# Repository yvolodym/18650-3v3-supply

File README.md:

# 18650-3v3-supply

Stabile 3,3-V-Versorgung aus einer 18650-Li-Ion-Zelle, inklusive USB-Ladung und Zellschutz.
KiCad-Projekt (KiCad 10).

## Blockschaltbild

```mermaid
flowchart LR
    USB["USB-C 5 V<br/>(P1)"] -->|VBUS| CHG["TP4056 (U1)<br/>Laden 0,9 A"]
    CHG -->|BAT+| BAT["18650 (BT1)<br/>+ DW01A / FS8205A<br/>Schutz"]
    BAT -->|BAT+| BOOST["MT3608 (U3)<br/>Boost 4,0 V<br/>über SS14"]
    BOOST -->|VBOOST| LDO["AP2112K-3.3 (U4)<br/>LDO"]
    LDO -->|+3V3| OUT["3,3 V<br/>(J1)"]
    BAT -->|"R8/R9 ÷2"| SENSE["VBAT_SENSE<br/>(J1 Pin 3)"]
```

1. **Laden** – USB-C-Buchse (P1, 5 V) → TP4056 (U1), Ladestrom ca. 0,9 A (R1 = 1,2 kΩ an PROG,
   laut Datenblatt-Tabelle; für 1 A: R1 = 1,1 kΩ). CC1/CC2 je 5,1 kΩ (R10/R11) nach GND, damit
   USB-C-Netzteile 5 V liefern.
   LEDs: D1 rot = lädt, D2 grün = voll. TEMP liegt an GND (NTC-Überwachung deaktiviert).
2. **Akku + Schutz** – 18650-Zelle (BT1) zwischen BAT+ und BAT−, DW01A (U5) + Dual-MOSFET FS8205A (Q1).
   Abschaltung bei Überladung 4,3 V / Tiefentladung 2,4 V / Überstrom.
   Systemmasse GND = P− (hinter dem FS8205A).
3. **Boost** – MT3608 (U3) mit L1 = 22 µH (≥ 2 A) und Schottky D3 (SS14) auf ca. 4,0 V (Netz `VBOOST`):
   `Vout = 0,6 V × (1 + R6/R7) = 0,6 × (1 + 22k/3,9k) ≈ 3,98 V`.
   Für 5 V Ausgang: R7 = 3 kΩ. Bei vollem Akku (4,2 V) taktet der Boost nur noch wenig (4,2 V − U_F(SS14) < 3,98 V), der LDO regelt.
4. **LDO** – AP2112K-3.3 (U4) aus `VBOOST` → stabile 3,3 V an J1 (Eingangsbereich Akku 2,4 … 4,2 V, untere Grenze = DW01A-Abschaltung).

**VBAT_SENSE:** Akkuspannung / 2 über Teiler R8/R9 (2 × 100 kΩ) für einen ADC.
Bei ca. 1,5 V (= 3,0 V Akku) sollte der Verbraucher in den Schlafmodus gehen.

## Anschlüsse

| Ref | Funktion | Pins |
|-----|----------|------|
| P1  | USB_5V_IN | USB-C-Buchse (GCT USB4105), nur VBUS/GND/CC1/CC2 genutzt |
| J1  | OUT_3V3   | 3-polig JST-EH (1 = +3V3, 2 = GND, 3 = VBAT_SENSE) |

## Stückliste (Hauptbauteile)

| Ref | Wert |
|-----|------|
| U1 | TP4056 Lade-IC |
| U5 | DW01A Akkuschutz |
| Q1 | FS8205A Dual-N-MOSFET |
| U3 | MT3608 Boost-Wandler |
| U4 | AP2112K-3.3 LDO |
| BT1 | 18650 Li-Ion |
| L1 | 22 µH / ≥ 2 A |
| D1, D2 | LED rot / grün |
| D3 | SS14 Schottky |
| C1–C8 | 10 µF, 10 µF, 100 nF, 3 × 22 µF, 1 µF, 10 µF |
| R1–R11 | 1,2k, 1k, 1k, 100R, 1k, 22k, 3,9k, 100k, 100k, 5,1k, 5,1k |
| P1 | USB-C-Buchse GCT USB4105 |
| J1 | JST EH 3-polig |

## Dateien

| Datei | Inhalt |
|-------|--------|
| `Akku_3V3_Versorgung.kicad_pro` | KiCad-Projekt |
| `Akku_3V3_Versorgung.kicad_sch` | Schaltplan |
| `Akku_3V3_Versorgung.kicad_pcb` | Platine (noch leer / nicht geroutet) |
| `Akku3V3.kicad_sym` | Projektlokale Symbolbibliothek |
| `sym-lib-table` | Bindet `Akku3V3` über `${KIPRJMOD}` ein |

## Status

- [x] Schaltplan
- [ ] Footprints zuweisen
- [ ] PCB-Layout
- [ ] Fertigungsdaten (Gerber/Bohrdaten werden nicht eingecheckt, siehe `.gitignore`)

## Lizenz

Copyright © 2026 Eugen Vladimirski

Dieses Projekt steht unter der **CERN Open Hardware Licence Version 2 – Strongly Reciprocal**
(SPDX: `CERN-OHL-S-2.0`), siehe [`LICENSE`](LICENSE).

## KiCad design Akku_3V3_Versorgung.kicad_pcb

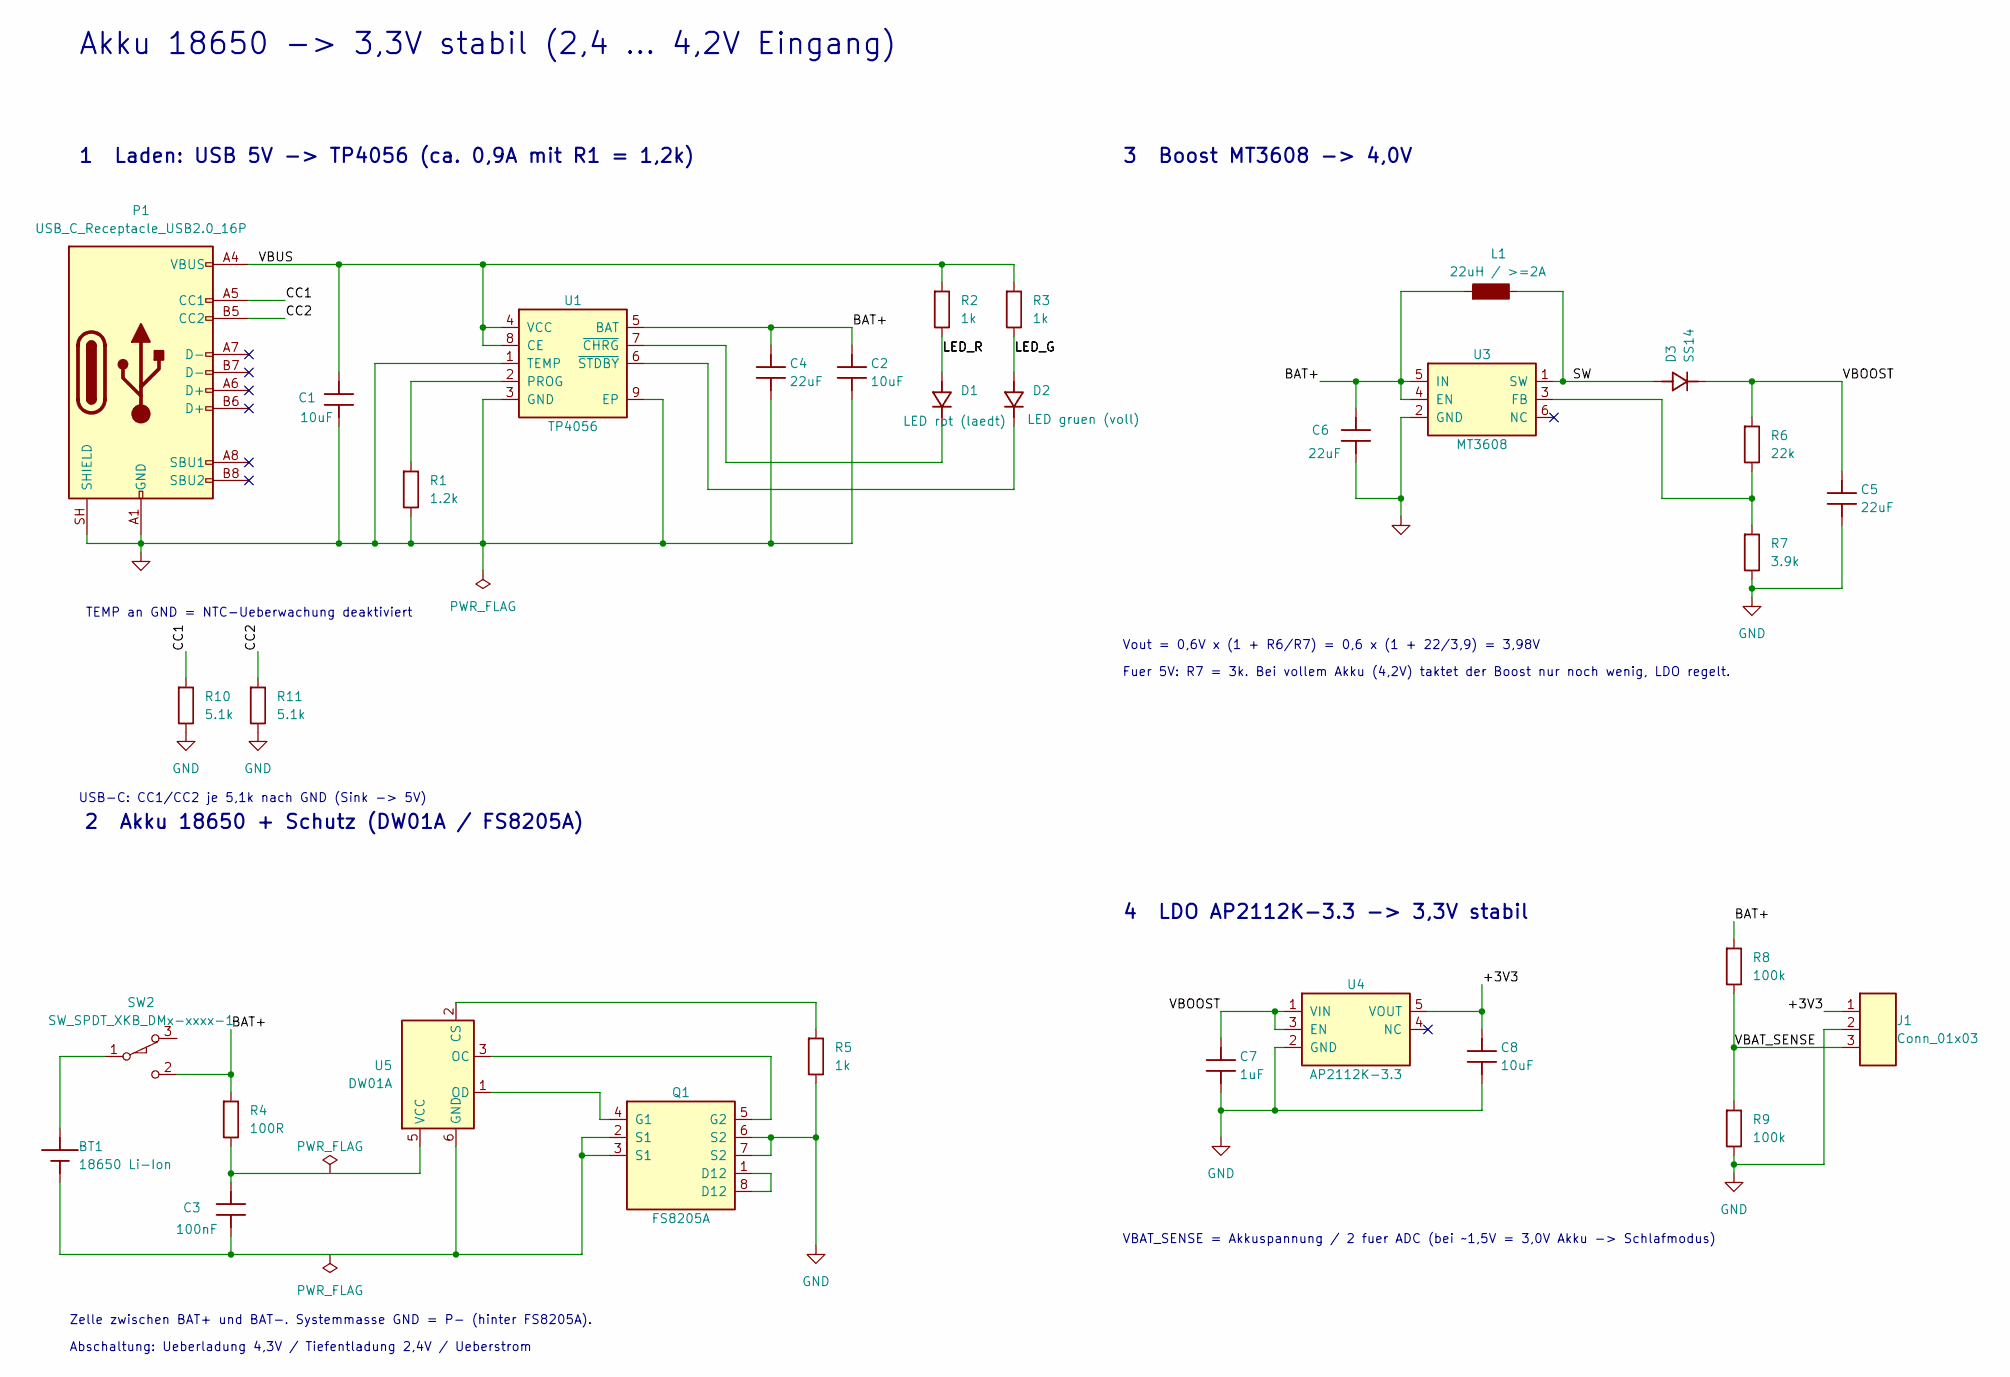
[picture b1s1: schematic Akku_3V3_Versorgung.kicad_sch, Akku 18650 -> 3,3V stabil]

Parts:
BT1: 18650 Li-Ion; NCR18650B
C1, C2, C8: 10uF; C_1206_3216Metric
C3: 100nF; C_1206_3216Metric
C4, C5, C6: 22uF; C_1206_3216Metric
C7: 1uF; C_1206_3216Metric
D1: LED rot (laedt); LED_D2.0mm_W4.8mm_H2.5mm_FlatTop
D2: LED gruen (voll); LED_D2.0mm_W4.8mm_H2.5mm_FlatTop
D3: SS14; D_SMA
J1: Conn_01x03; JST_EH_B3B-EH-A_1x03_P2.50mm_Vertical
L1: 22uH / >=2A; L_1206_3216Metric
P1: USB_C_Receptacle_USB2.0_16P; USB_C_Receptacle_GCT_USB4105-xx-A_16P_TopMnt_Horizontal
Q1: FS8205A; TSSOP-8_4.4x3mm_P0.65mm
R1: 1.2k; R_1206_3216Metric
R2, R3, R5: 1k; R_1206_3216Metric
R4: 100R; R_1206_3216Metric
R6: 22k; R_1206_3216Metric
R7: 3.9k; R_1206_3216Metric
R8, R9: 100k; R_1206_3216Metric
R10, R11: 5.1k; R_1206_3216Metric
SW2: SW_SPDT_XKB_DMx-xxxx-1; Switch_Small
U1: TP4056; SOIC-8-1EP_3.9x4.9mm_P1.27mm_EP2.29x3mm
U3: MT3608; SOT-23-6
U4: AP2112K-3.3; SOT-23-5
U5: DW01A; SOT-23-6

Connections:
/+3V3: C8.1, J1.1, U4.5 (VOUT)
/BAT+: C2.1, C4.1, C6.1, L1.1, R4.1, R8.1, SW2.2 (B), U1.5 (BAT), U3.4 (EN), U3.5 (IN)
/CC1: P1.A5 (CC1), R10.1
/CC2: P1.B5 (CC2), R11.1
/LED_G: D2.2 (A), R3.2
/LED_R: D1.2 (A), R2.2
/SW: D3.2 (A), L1.2, U3.1 (SW)
/VBAT_SENSE: J1.3, R8.2, R9.1
/VBOOST: C5.1, C7.1, D3.1 (K), R6.1, U4.1 (VIN), U4.3 (EN)
/VBUS: C1.1, P1.A4 (VBUS), P1.A9 (VBUS), P1.B4 (VBUS), P1.B9 (VBUS), R2.1, R3.1, U1.4 (VCC), U1.8 (CE)
GND: C1.2, C2.2, C4.2, C5.2, C6.2, C7.2, C8.2, J1.2, P1.A1 (GND), P1.A12 (GND), P1.B1 (GND), P1.B12 (GND), P1.SH (SHIELD), Q1.6 (S2), Q1.7 (S2), R1.2, R5.2, R7.2, R9.2, R10.2, R11.2, U1.1 (TEMP), U1.3 (GND), U1.9 (EP), U3.2 (GND), U4.2 (GND)
unnamed: BT1.1 (+), SW2.1 (A)
unnamed 12: BT1.2 (-), C3.2, Q1.2 (S1), Q1.3 (S1), U5.6 (GND); also elsewhere on the board
unnamed: D1.1 (K), U1.7 (~CHRG)
unnamed: D2.1 (K), U1.6 (~STDBY)
unnamed: Q1.1 (D12), Q1.8 (D12)
unnamed 16: Q1.4 (G1), U5.1 (OD); also elsewhere on the board
unnamed 17: Q1.5 (G2), U5.3 (OC); also elsewhere on the board
unnamed: R1.1, U1.2 (PROG)
unnamed: R6.2, R7.1, U3.3 (FB)
unnamed: R5.1, U5.2 (CS)
unnamed: C3.1, R4.2, U5.5 (VCC)

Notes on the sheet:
1 Laden: USB 5V -> TP4056 (ca. 0,9A mit R1 = 1,2k)
Akku 18650 -> 3,3V stabil (2,4 ... 4,2V Eingang)
VBAT_SENSE = Akkuspannung / 2 fuer ADC (bei ~1,5V = 3,0V Akku -> Schlafmodus)
Fuer 5V: R7 = 3k. Bei vollem Akku (4,2V) taktet der Boost nur noch wenig, LDO regelt.
3 Boost MT3608 -> 4,0V
Vout = 0,6V x (1 + R6/R7) = 0,6 x (1 + 22/3,9) = 3,98V
Abschaltung: Ueberladung 4,3V / Tiefentladung 2,4V / Ueberstrom
4 LDO AP2112K-3.3 -> 3,3V stabil
Zelle zwischen BAT+ und BAT-. Systemmasse GND = P- (hinter FS8205A).
USB-C: CC1/CC2 je 5,1k nach GND (Sink -> 5V)
2 Akku 18650 + Schutz (DW01A / FS8205A)
TEMP an GND = NTC-Ueberwachung deaktiviert

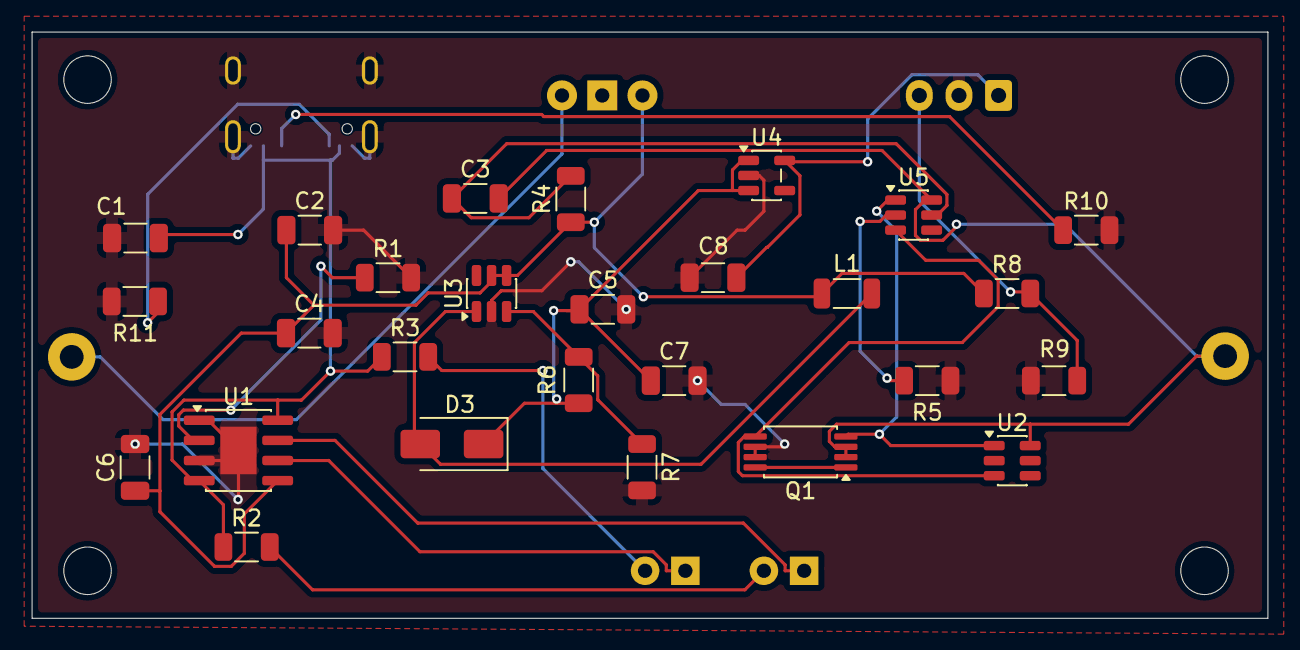
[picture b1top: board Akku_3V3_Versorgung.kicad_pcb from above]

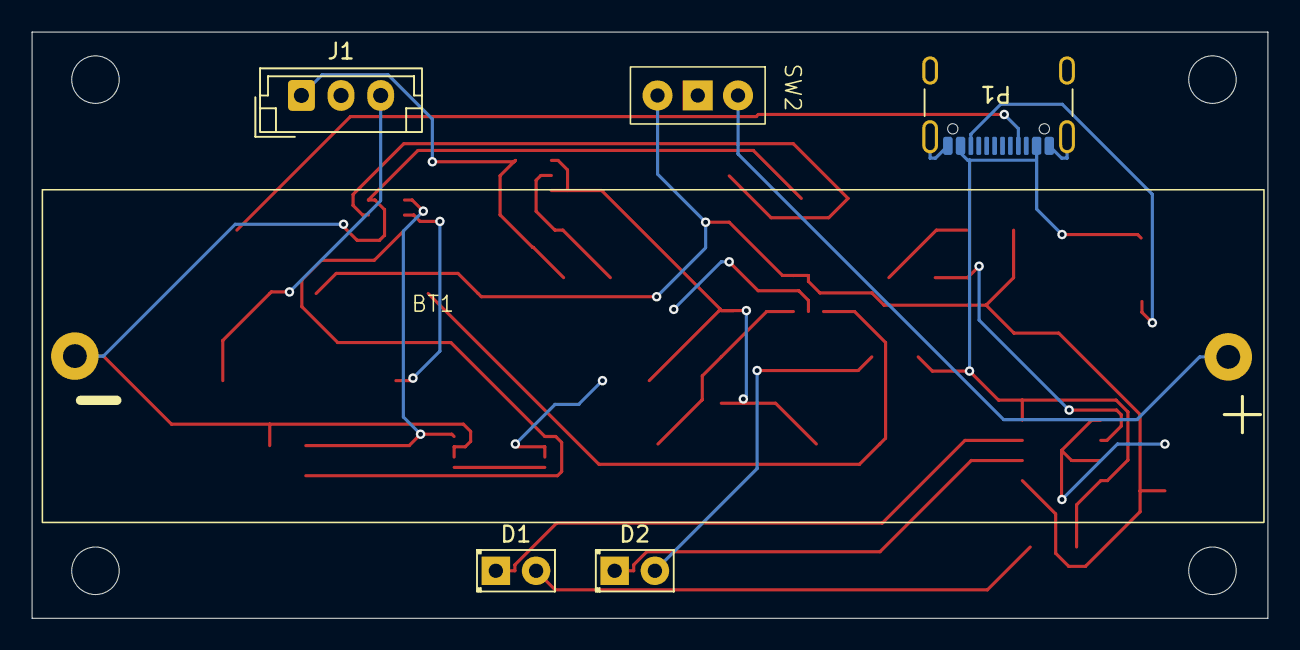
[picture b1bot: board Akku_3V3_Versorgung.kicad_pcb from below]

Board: 2 copper layers, 78.0 x 37.0 mm, 33 parts (6 on the bottom side), 22 nets.

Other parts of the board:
U2: DW01A; SOT-23-6

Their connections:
unnamed 12: U2.6 (GND); also elsewhere on the board
unnamed 16: U2.1 (OD); also elsewhere on the board
unnamed 17: U2.3 (OC); also elsewhere on the board
